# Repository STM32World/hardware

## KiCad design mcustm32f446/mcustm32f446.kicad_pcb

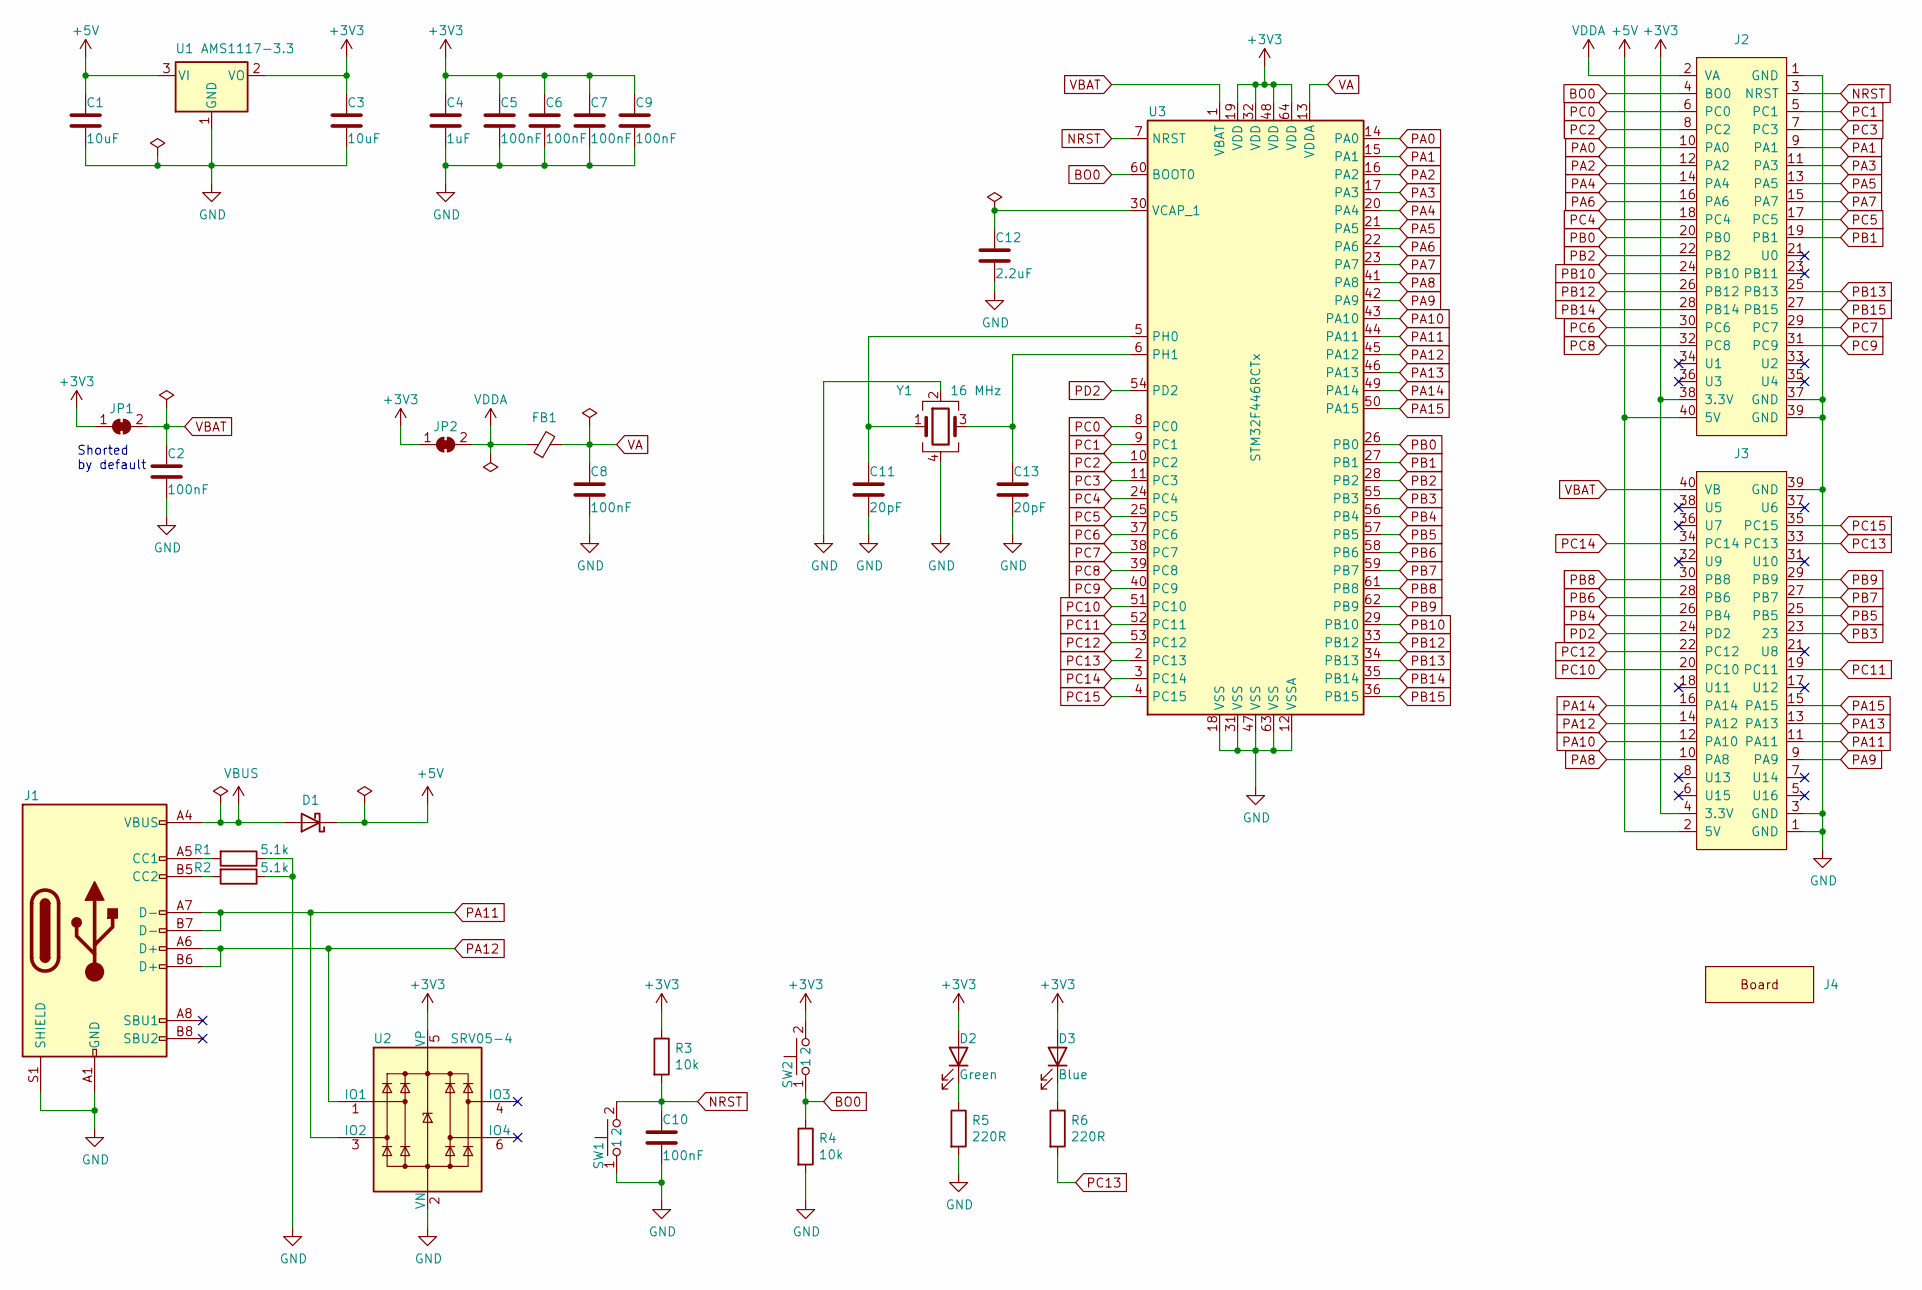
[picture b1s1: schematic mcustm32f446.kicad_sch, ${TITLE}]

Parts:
C1, C3: C_10UF_0805; C_0805_2012Metric; LCSC C15850
C2, C5, C6, C7, C8, C9, C10: C_100NF_0603; C_0603_1608Metric; LCSC C14663
C4: C_1UF_0603; C_0603_1608Metric; LCSC C15849
C11, C13: C_20PF_0603; C_0603_1608Metric; LCSC C1648
C12: C_2.2UF_0603; C_0603_1608Metric; LCSC C23630
D1: D_SOD-123; LCSC C8598
D2: LED_GREEN_0603; LED_0603_1608Metric; LCSC C72043
D3: LED_BLUE_0603; LED_0603_1608Metric; LCSC C72041
FB1: FB_0603; L_0603_1608Metric; LCSC C1002
J1: USB_C_Receptacle_HRO_TYPE-C-31-M-12; LCSC C165948
J2: STM32WORLD_CONNECTOR_1; PinSocket_2x20_P2.54mm_Vertical_Stackable; LCSC C35165
J3: STM32WORLD_CONNECTOR_2; PinSocket_2x20_P2.54mm_Vertical_Stackable; LCSC C35165
J4: STM32WORLD_BOARD
JP1, JP2: SolderJumper_2_Bridged; SolderJumper-2_P1.3mm_Bridged_RoundedPad1.0x1.5mm
R1, R2: R_5.1K_0603; R_0603_1608Metric; LCSC C23186
R3, R4: R_10K_0603; R_0603_1608Metric; LCSC C25804
R5, R6: R_220_0603; R_0603_1608Metric; LCSC C22962
SW1, SW2: TS-1088R-02526; LCSC C455281
U1: AMS1117-3.3; SOT-223-3_TabPin2; LCSC C6186
U2: SRV05-4; SOT-23-6; LCSC C85364
U3: STM32F446RCTx; LQFP-64_10x10mm_P0.5mm; LCSC C915971
Y1: X_16MHZ; Crystal_SMD_3225-4Pin_3.2x2.5mm; LCSC C13738

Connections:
+3V3: C3.1, C4.1, C5.1, C6.1, C7.1, C9.1, D2.2 (A), D3.2 (A), J2.38 (3.3V), J3.4 (3.3V), JP1.1 (A), JP2.1 (A), R3.1, SW2.2, U1.2 (VO), U2.5 (VP), U3.19 (VDD), U3.32 (VDD), U3.48 (VDD), U3.64 (VDD)
+5V: C1.1, D1.1 (K), J2.40 (5V), J3.2 (5V), U1.3 (VI)
BO0: J2.4 (BO0), R4.1, SW2.1, U3.60 (BOOT0)
GND: C1.2, C2.2, C3.2, C4.2, C5.2, C6.2, C7.2, C8.2, C9.2, C10.2, C11.2, C12.2, C13.2, J1.A1 (GND), J1.A12 (GND), J1.B1 (GND), J1.B12 (GND), J1.S1 (SHIELD), J2.1 (GND), J2.37 (GND), J2.39 (GND), J3.1 (GND), J3.3 (GND), J3.39 (GND), R1.1, R2.1, R4.2, R5.2, SW1.1, U1.1 (GND), U2.2 (VN), U3.12 (VSSA), U3.18 (VSS), U3.31 (VSS), U3.47 (VSS), U3.63 (VSS), Y1.2, Y1.4
NRST: C10.1, J2.3 (NRST), R3.2, SW1.2, U3.7 (NRST)
unnamed: C11.1, U3.5 (PH0), Y1.1
unnamed: C12.1, U3.30 (VCAP_1)
unnamed: C13.1, U3.6 (PH1), Y1.3
unnamed: D2.1 (K), R5.1
unnamed: D3.1 (K), R6.1
unnamed: J1.A5 (CC1), R1.2
unnamed: J1.B5 (CC2), R2.2
PA0: J2.10 (PA0), U3.14 (PA0)
PA1: J2.9 (PA1), U3.15 (PA1)
PA2: J2.12 (PA2), U3.16 (PA2)
PA3: J2.11 (PA3), U3.17 (PA3)
PA4: J2.14 (PA4), U3.20 (PA4)
PA5: J2.13 (PA5), U3.21 (PA5)
PA6: J2.16 (PA6), U3.22 (PA6)
PA7: J2.15 (PA7), U3.23 (PA7)
PA8: J3.10 (PA8), U3.41 (PA8)
PA9: J3.9 (PA9), U3.42 (PA9)
PA10: J3.12 (PA10), U3.43 (PA10)
PA11: J1.A7 (D-), J1.B7 (D-), J3.11 (PA11), U2.3 (IO2), U3.44 (PA11)
PA12: J1.A6 (D+), J1.B6 (D+), J3.14 (PA12), U2.1 (IO1), U3.45 (PA12)
PA13: J3.13 (PA13), U3.46 (PA13)
PA14: J3.16 (PA14), U3.49 (PA14)
PA15: J3.15 (PA15), U3.50 (PA15)
PB0: J2.20 (PB0), U3.26 (PB0)
PB1: J2.19 (PB1), U3.27 (PB1)
PB2: J2.22 (PB2), U3.28 (PB2)
PB3: J3.23, U3.55 (PB3)
PB4: J3.26 (PB4), U3.56 (PB4)
PB5: J3.25 (PB5), U3.57 (PB5)
PB6: J3.28 (PB6), U3.58 (PB6)
PB7: J3.27 (PB7), U3.59 (PB7)
PB8: J3.30 (PB8), U3.61 (PB8)
PB9: J3.29 (PB9), U3.62 (PB9)
PB10: J2.24 (PB10), U3.29 (PB10)
PB12: J2.26 (PB12), U3.33 (PB12)
PB13: J2.25 (PB13), U3.34 (PB13)
PB14: J2.28 (PB14), U3.35 (PB14)
PB15: J2.27 (PB15), U3.36 (PB15)
PC0: J2.6 (PC0), U3.8 (PC0)
PC1: J2.5 (PC1), U3.9 (PC1)
PC2: J2.8 (PC2), U3.10 (PC2)
PC3: J2.7 (PC3), U3.11 (PC3)
PC4: J2.18 (PC4), U3.24 (PC4)
PC5: J2.17 (PC5), U3.25 (PC5)
PC6: J2.30 (PC6), U3.37 (PC6)
PC7: J2.29 (PC7), U3.38 (PC7)
PC8: J2.32 (PC8), U3.39 (PC8)
PC9: J2.31 (PC9), U3.40 (PC9)
PC10: J3.20 (PC10), U3.51 (PC10)
PC11: J3.19 (PC11), U3.52 (PC11)
PC12: J3.22 (PC12), U3.53 (PC12)
PC13: J3.33 (PC13), R6.2, U3.2 (PC13)
PC14: J3.34 (PC14), U3.3 (PC14)
PC15: J3.35 (PC15), U3.4 (PC15)
PD2: J3.24 (PD2), U3.54 (PD2)
VA: C8.1, FB1.2, U3.13 (VDDA)
VBAT: C2.1, J3.40 (VB), JP1.2 (B), U3.1 (VBAT)
VBUS: D1.2 (A), J1.A4 (VBUS), J1.A9 (VBUS), J1.B4 (VBUS), J1.B9 (VBUS)
VDDA: FB1.1, J2.2 (VA), JP2.2 (B)

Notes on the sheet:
Shorted by default

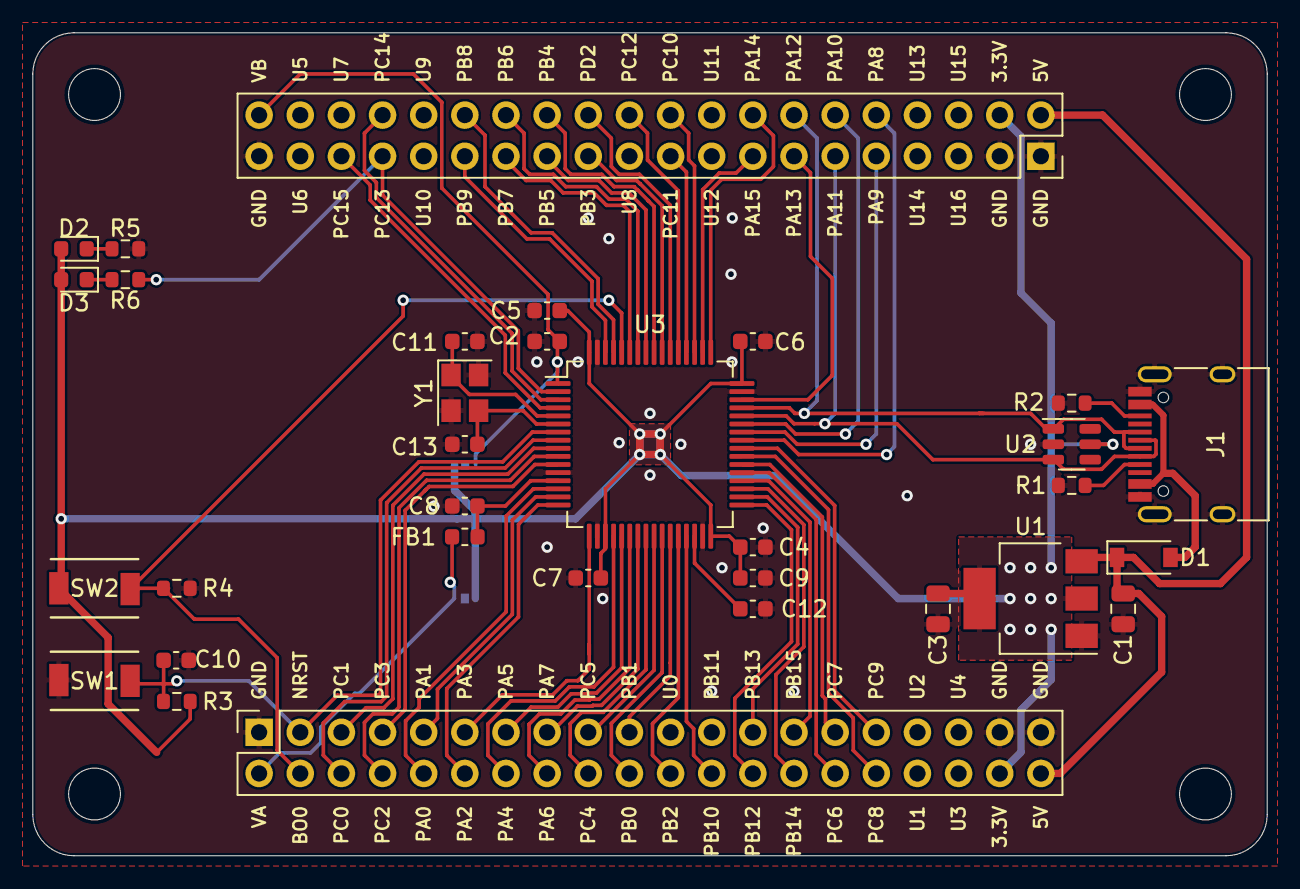
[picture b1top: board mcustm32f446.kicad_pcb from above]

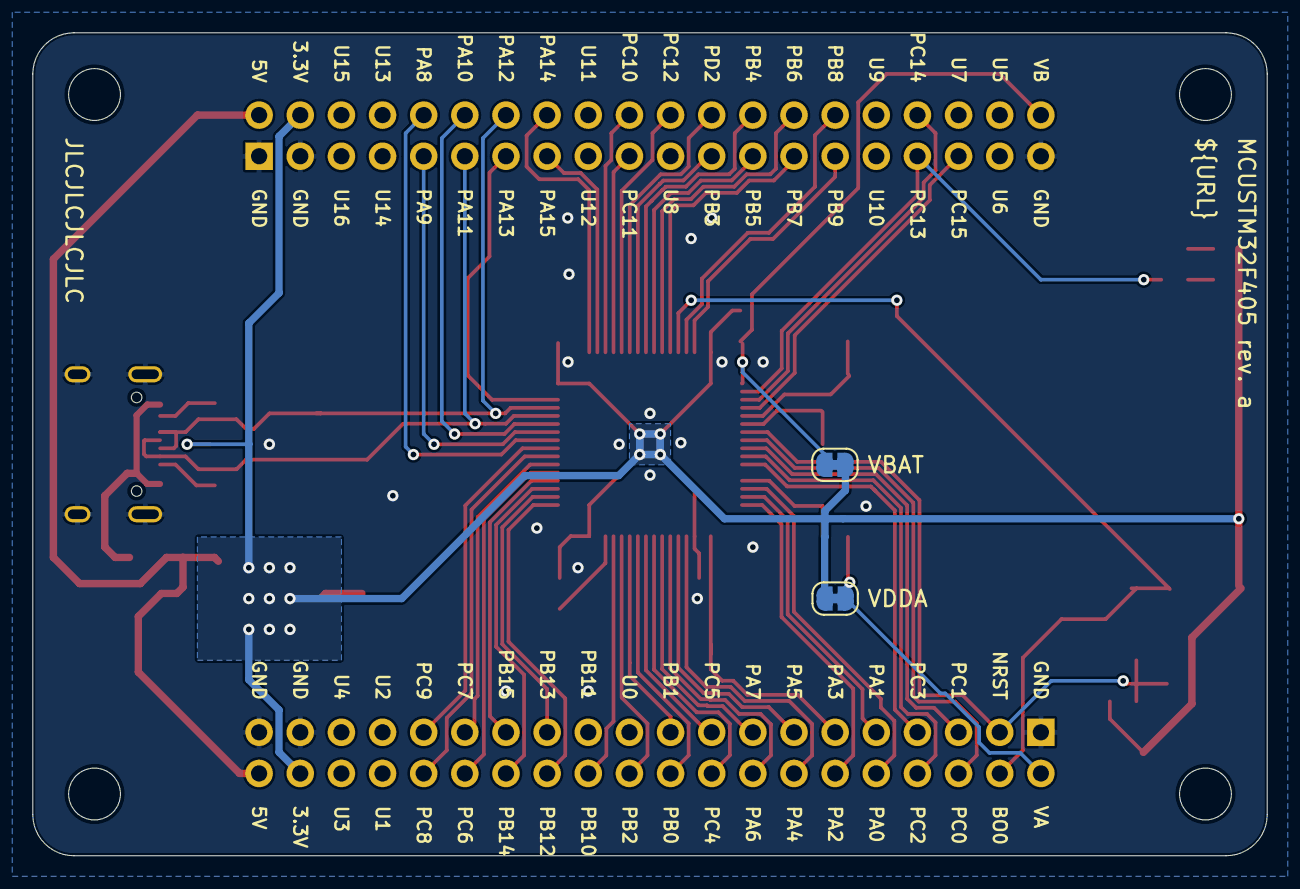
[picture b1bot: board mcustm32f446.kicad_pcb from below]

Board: 2 copper layers, 76.2 x 50.8 mm, 35 parts (2 on the bottom side), 64 nets.

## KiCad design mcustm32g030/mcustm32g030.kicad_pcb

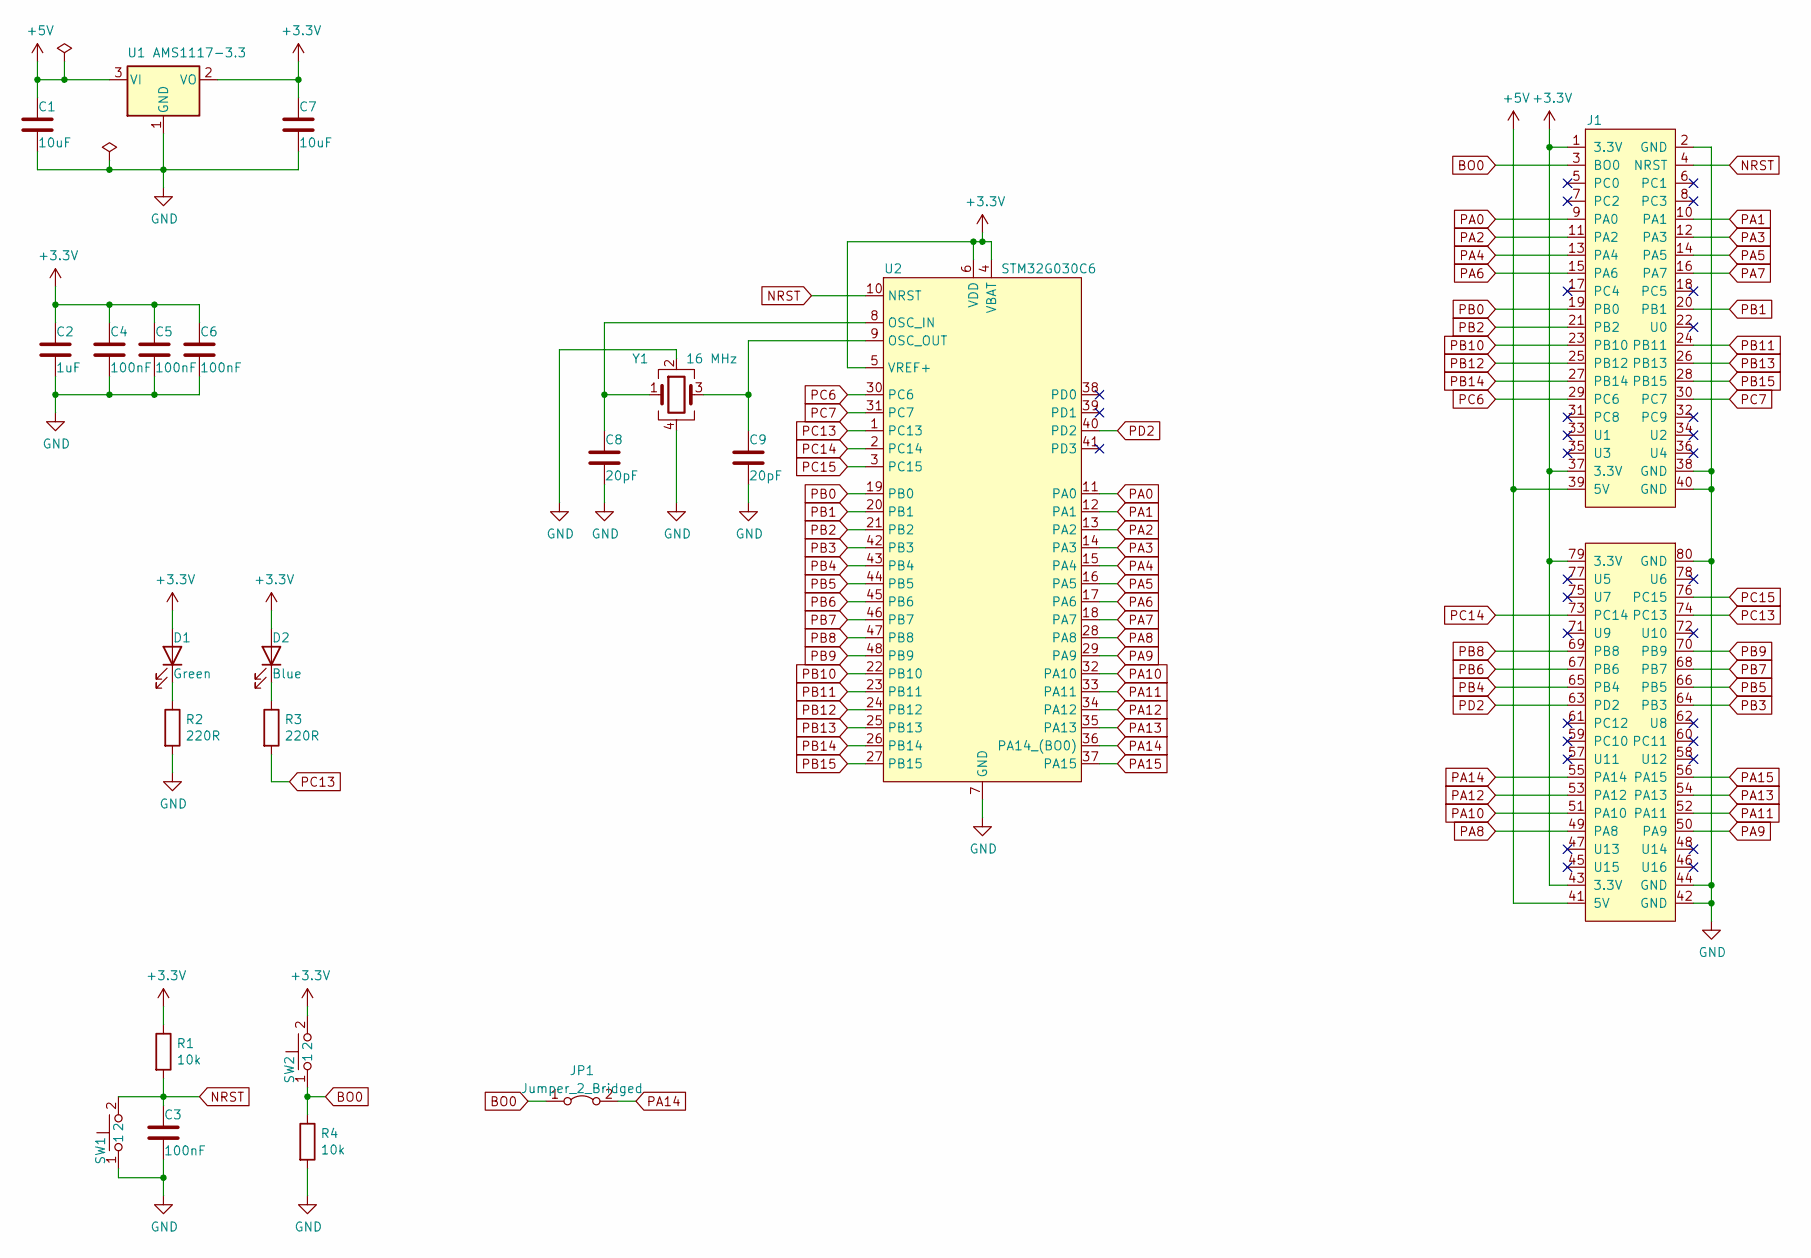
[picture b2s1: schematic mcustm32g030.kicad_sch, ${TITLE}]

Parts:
C1, C7: 10uF; C_0805_2012Metric; LCSC C15850
C2: 1uF; C_0603_1608Metric; LCSC C15849
C3, C4, C5, C6: 100nF; C_0603_1608Metric; LCSC C14663
C8, C9: 20pF; C_0603_1608Metric; LCSC C1648
D1: GR; LED_0603_1608Metric; LCSC C72043
D2: BL; LED_0603_1608Metric; LCSC C72041
J1: STM32WORLD_BASE
JP1: Jumper_2_Bridged; SolderJumper-2_P1.3mm_Bridged2Bar_Pad1.0x1.5mm
R1, R4: 10k; R_0603_1608Metric; LCSC C25804
R2, R3: 220R; R_0603_1608Metric; LCSC C22962
SW1, SW2: TS-1088R-02526; LCSC C455281
U1: AMS1117-3.3; SOT-223-3_TabPin2; LCSC C6186
U2: STM32G030C6; LQFP-48_7x7mm_P0.5mm; LCSC C529328
Y1: X_16MHZ; Crystal_SMD_3225-4Pin_3.2x2.5mm; LCSC C13738

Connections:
+3V3: C2.1, C4.1, C5.1, C6.1, C7.1, D1.2 (A), D2.2 (A), J1.1 (3.3V), J1.37 (3.3V), J1.43 (3.3V), J1.79 (3.3V), R1.1, SW2.2, U1.2 (VO), U2.4 (VBAT), U2.5 (VREF+), U2.6 (VDD)
+5V: C1.1, J1.39 (5V), J1.41 (5V), U1.3 (VI)
BO0: J1.3 (BO0), JP1.1 (A), R4.1, SW2.1
GND: C1.2, C2.2, C3.2, C4.2, C5.2, C6.2, C7.2, C8.2, C9.2, J1.2 (GND), J1.38 (GND), J1.40 (GND), J1.42 (GND), J1.44 (GND), J1.80 (GND), R2.2, R4.2, SW1.1, U1.1 (GND), U2.7 (GND), Y1.2, Y1.4
NRST: C3.1, J1.4 (NRST), R1.2, SW1.2, U2.10 (NRST)
unnamed: C8.1, U2.8 (OSC_IN), Y1.1
unnamed: C9.1, U2.9 (OSC_OUT), Y1.3
unnamed: D1.1 (K), R2.1
unnamed: D2.1 (K), R3.1
PA0: J1.9 (PA0), U2.11 (PA0)
PA1: J1.10 (PA1), U2.12 (PA1)
PA2: J1.11 (PA2), U2.13 (PA2)
PA3: J1.12 (PA3), U2.14 (PA3)
PA4: J1.13 (PA4), U2.15 (PA4)
PA5: J1.14 (PA5), U2.16 (PA5)
PA6: J1.15 (PA6), U2.17 (PA6)
PA7: J1.16 (PA7), U2.18 (PA7)
PA8: J1.49 (PA8), U2.28 (PA8)
PA9: J1.50 (PA9), U2.29 (PA9)
PA10: J1.51 (PA10), U2.32 (PA10)
PA11: J1.52 (PA11), U2.33 (PA11)
PA12: J1.53 (PA12), U2.34 (PA12)
PA13: J1.54 (PA13), U2.35 (PA13)
PA14: J1.55 (PA14), JP1.2 (B), U2.36 (PA14_(BO0))
PA15: J1.56 (PA15), U2.37 (PA15)
PB0: J1.19 (PB0), U2.19 (PB0)
PB1: J1.20 (PB1), U2.20 (PB1)
PB2: J1.21 (PB2), U2.21 (PB2)
PB3: J1.64 (PB3), U2.42 (PB3)
PB4: J1.65 (PB4), U2.43 (PB4)
PB5: J1.66 (PB5), U2.44 (PB5)
PB6: J1.67 (PB6), U2.45 (PB6)
PB7: J1.68 (PB7), U2.46 (PB7)
PB8: J1.69 (PB8), U2.47 (PB8)
PB9: J1.70 (PB9), U2.48 (PB9)
PB10: J1.23 (PB10), U2.22 (PB10)
PB11: J1.24 (PB11), U2.23 (PB11)
PB12: J1.25 (PB12), U2.24 (PB12)
PB13: J1.26 (PB13), U2.25 (PB13)
PB14: J1.27 (PB14), U2.26 (PB14)
PB15: J1.28 (PB15), U2.27 (PB15)
PC6: J1.29 (PC6), U2.30 (PC6)
PC7: J1.30 (PC7), U2.31 (PC7)
PC13: J1.74 (PC13), R3.2, U2.1 (PC13)
PC14: J1.73 (PC14), U2.2 (PC14)
PC15: J1.76 (PC15), U2.3 (PC15)
PD2: J1.63 (PD2), U2.40 (PD2)

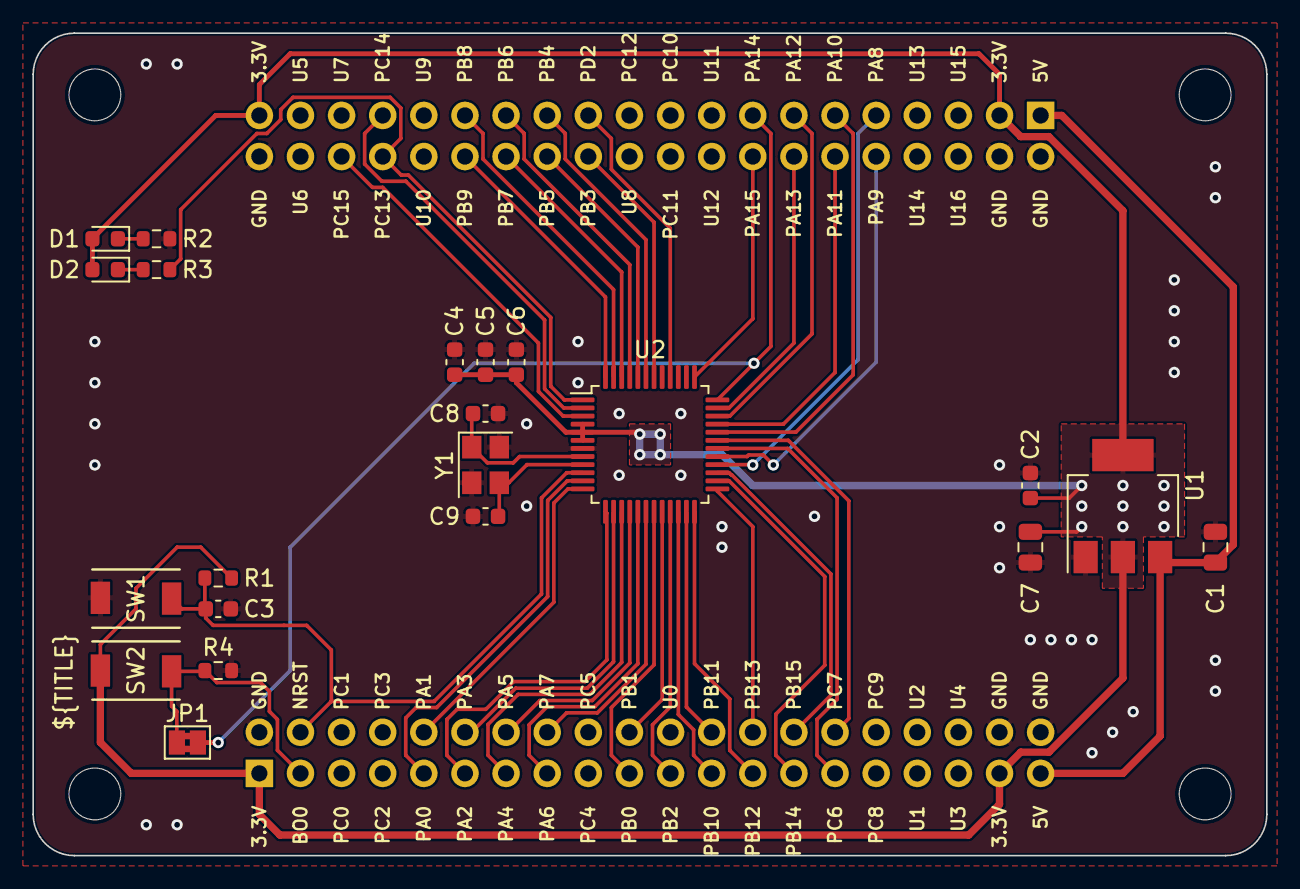
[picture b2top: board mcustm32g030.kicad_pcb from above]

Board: 2 copper layers, 76.2 x 50.8 mm, 22 parts (0 on the bottom side), 47 nets.

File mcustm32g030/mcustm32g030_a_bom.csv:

Comment,Designator,Footprint,Display,LCSC
"10uF","C1,C7","Capacitor_SMD:C_0805_2012Metric","10uF","C15850"
"1uF","C2","Capacitor_SMD:C_0603_1608Metric","1uF","C15849"
"100nF","C3,C4,C5,C6","Capacitor_SMD:C_0603_1608Metric","100nF","C14663"
"20pF","C8,C9","Capacitor_SMD:C_0603_1608Metric","20pF","C1648"
"GR","D1","LED_SMD:LED_0603_1608Metric","Green","C72043"
"BL","D2","LED_SMD:LED_0603_1608Metric","Blue","C72041"
"STM32WORLD_BASE","J1","stm32world:STM32WORLD_BASE"
"Jumper_2_Bridged","JP1","Jumper:SolderJumper-2_P1.3mm_Bridged2Bar_Pad1.0x1.5mm"
"10k","R1,R4","Resistor_SMD:R_0603_1608Metric","10k","C25804"
"220R","R2,R3","Resistor_SMD:R_0603_1608Metric","220R","C22962"
"~","SW1,SW2","stm32world:TS-1088R-02526","","C455281"
"AMS1117-3.3","U1","Package_TO_SOT_SMD:SOT-223-3_TabPin2","","C6186"
"STM32G030C6","U2","Package_QFP:LQFP-48_7x7mm_P0.5mm","","C529328"
"X_16MHZ","Y1","Crystal:Crystal_SMD_3225-4Pin_3.2x2.5mm","16 MHz","C13738"

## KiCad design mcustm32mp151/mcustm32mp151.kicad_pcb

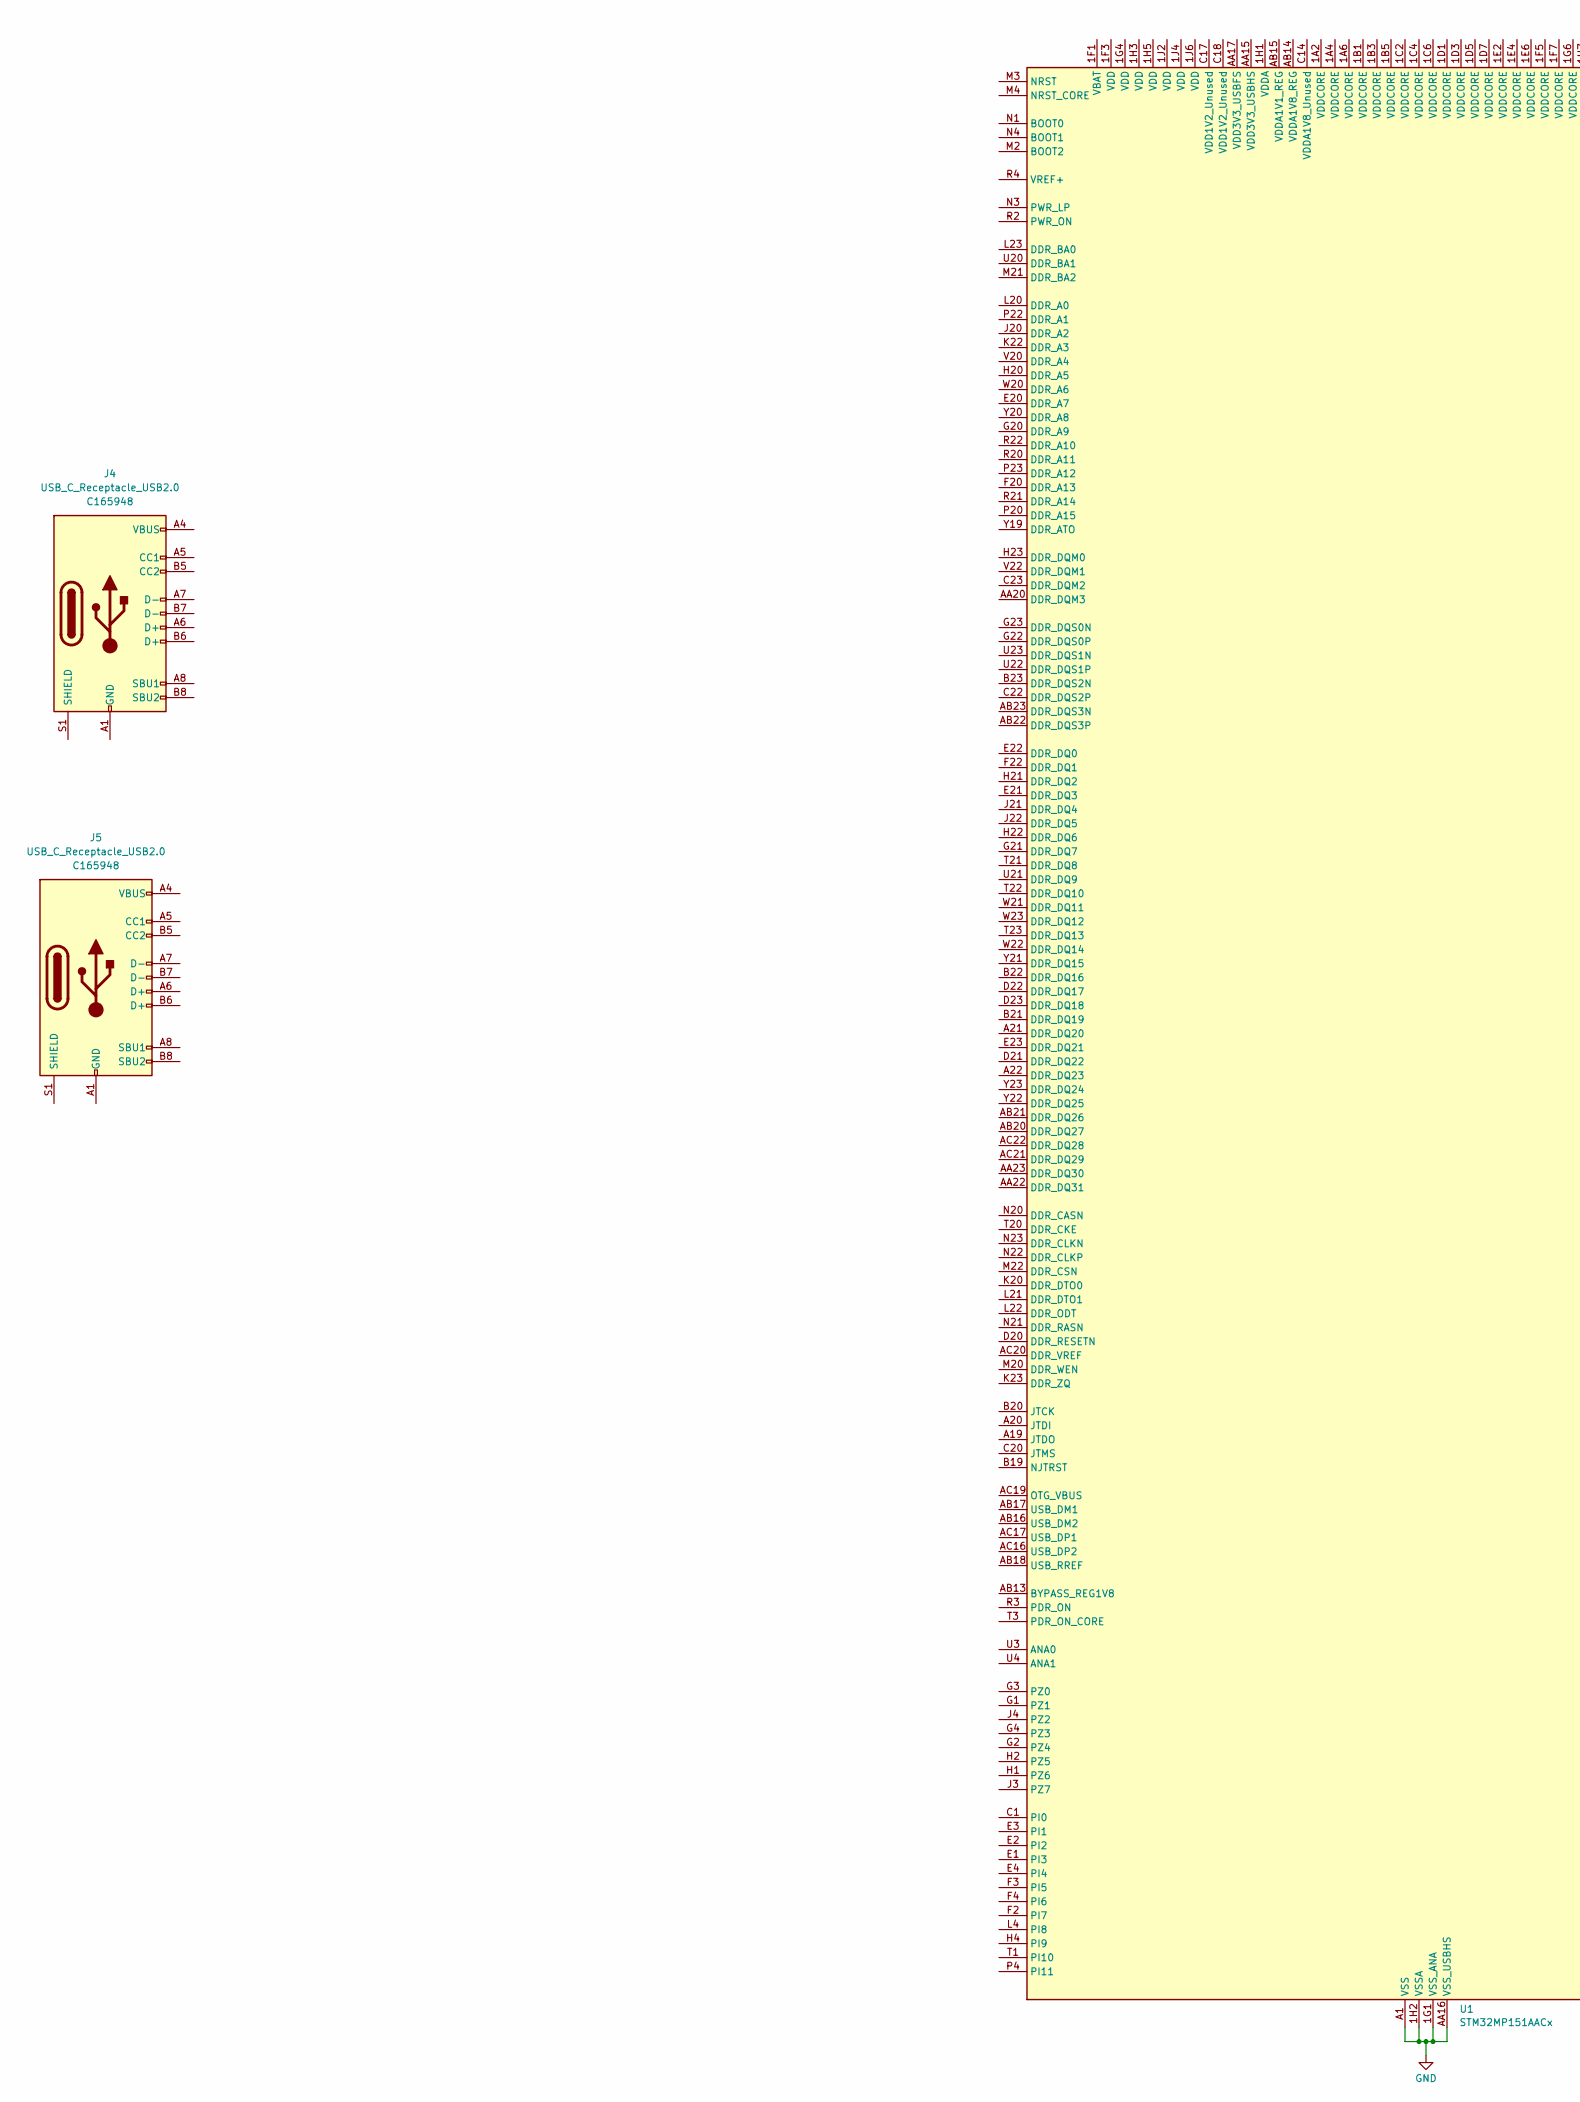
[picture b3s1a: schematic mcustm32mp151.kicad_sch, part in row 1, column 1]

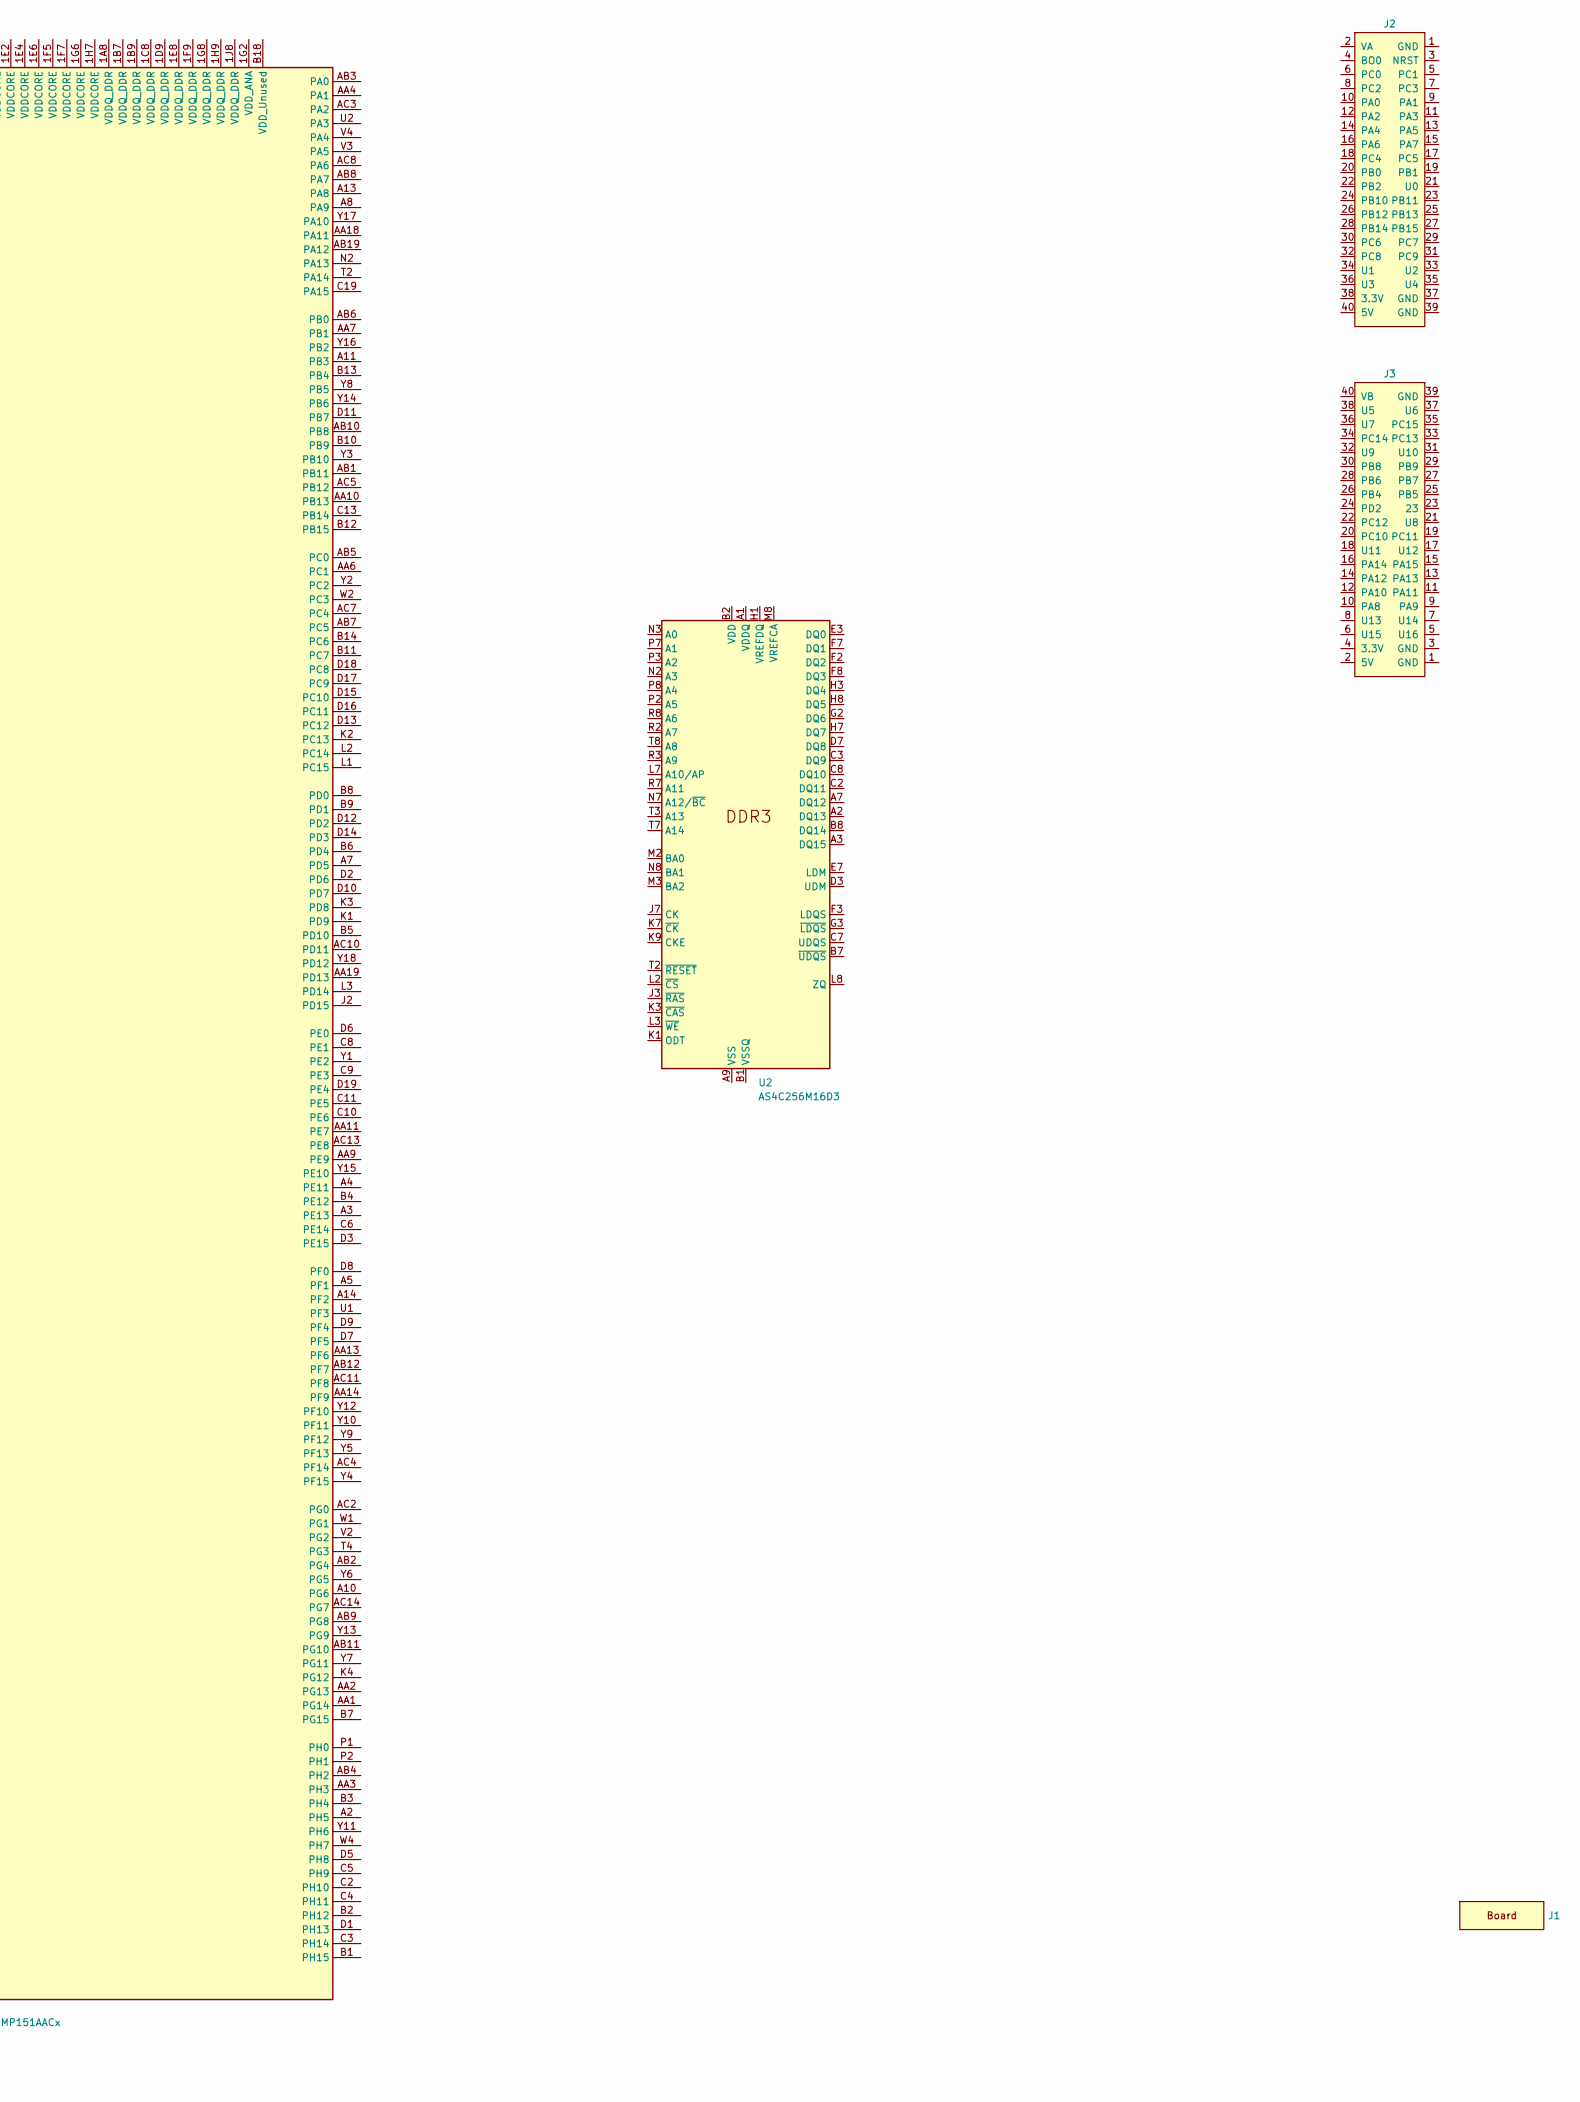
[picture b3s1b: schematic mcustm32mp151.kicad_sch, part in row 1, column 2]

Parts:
J1: STM32WORLD_BOARD
J2: STM32WORLD_CONNECTOR_1; PinSocket_2x20_P2.54mm_Vertical_Stackable; LCSC C35165
J3: STM32WORLD_CONNECTOR_2; PinSocket_2x20_P2.54mm_Vertical_Stackable; LCSC C35165
J4, J5: USB_C_Receptacle_USB2.0; USB_C_Receptacle_HRO_TYPE-C-31-M-12; LCSC C165948
U1: STM32MP151AACx; ST_TFBGA-361_12x12mm_Layout23x23_P0.5mmP0.65mm; LCSC C1555473
U2: AS4C256M16D3; BGA-96_9.0x13.0mm_Layout2x3x16_P0.8mm

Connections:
GND: U1.1A3 (VSS), U1.1A5 (VSS), U1.1A7 (VSS), U1.1B2 (VSS), U1.1B4 (VSS), U1.1B6 (VSS), U1.1B8 (VSS), U1.1C1 (VSS), U1.1C3 (VSS), U1.1C5 (VSS), U1.1C7 (VSS), U1.1C9 (VSS), U1.1D2 (VSS), U1.1D4 (VSS), U1.1D6 (VSS), U1.1D8 (VSS), U1.1E1 (VSS), U1.1E3 (VSS), U1.1E5 (VSS), U1.1E7 (VSS), U1.1E9 (VSS), U1.1F2 (VSS), U1.1F4 (VSS), U1.1F6 (VSS), U1.1F8 (VSS), U1.1G1 (VSS_ANA), U1.1G3 (VSS), U1.1G5 (VSS), U1.1G7 (VSS), U1.1G9 (VSS), U1.1H2 (VSSA), U1.1H4 (VSS), U1.1H6 (VSS), U1.1H8 (VSS), U1.1J3 (VSS), U1.1J5 (VSS), U1.1J7 (VSS), U1.A1 (VSS), U1.A23 (VSS), U1.AA5 (VSS), U1.AA8 (VSS), U1.AA12 (VSS), U1.AA16 (VSS_USBHS), U1.AA21 (VSS), U1.AC1 (VSS), U1.AC23 (VSS), U1.C7 (VSS), U1.C12 (VSS), U1.C16 (VSS), U1.C21 (VSS), U1.D4 (VSS), U1.F21 (VSS), U1.H3 (VSS), U1.K21 (VSS), U1.P3 (VSS), U1.P21 (VSS), U1.V21 (VSS), U1.W3 (VSS)
unnamed: J4.A1 (GND), J4.A12 (GND), J4.B1 (GND), J4.B12 (GND)
unnamed: J4.A4 (VBUS), J4.A9 (VBUS), J4.B4 (VBUS), J4.B9 (VBUS)
unnamed: J5.A1 (GND), J5.A12 (GND), J5.B1 (GND), J5.B12 (GND)
unnamed: J5.A4 (VBUS), J5.A9 (VBUS), J5.B4 (VBUS), J5.B9 (VBUS)
unnamed: U2.B2 (VDD), U2.D9 (VDD), U2.G7 (VDD), U2.K2 (VDD), U2.K8 (VDD), U2.N1 (VDD), U2.N9 (VDD), U2.R1 (VDD), U2.R9 (VDD)
unnamed: U2.A1 (VDDQ), U2.A8 (VDDQ), U2.C1 (VDDQ), U2.C9 (VDDQ), U2.D2 (VDDQ), U2.E9 (VDDQ), U2.F1 (VDDQ), U2.H2 (VDDQ), U2.H9 (VDDQ)
unnamed: U2.A9 (VSS), U2.B3 (VSS), U2.E1 (VSS), U2.G8 (VSS), U2.J2 (VSS), U2.J8 (VSS), U2.M1 (VSS), U2.M9 (VSS), U2.P1 (VSS), U2.P9 (VSS), U2.T1 (VSS), U2.T9 (VSS)
unnamed: U2.B1 (VSSQ), U2.B9 (VSSQ), U2.D1 (VSSQ), U2.D8 (VSSQ), U2.E2 (VSSQ), U2.E8 (VSSQ), U2.F9 (VSSQ), U2.G1 (VSSQ), U2.G9 (VSSQ)

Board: 8 copper layers, 7 parts (0 on the bottom side), 9 nets, no tracks yet.

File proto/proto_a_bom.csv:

Comment,Designator,Footprint,LCSC
"STM32WORLD_CONNECTOR_2","J1","stm32world:PinSocket_2x20_P2.54mm_Vertical_Stackable","C35165"
"STM32WORLD_CONNECTOR_1","J2","stm32world:PinSocket_2x20_P2.54mm_Vertical_Stackable","C35165"
"STM32WORLD_BOARD","J3","stm32world:STM32WORLD_BOARD"
"TestPoint_Small","TP1,TP2,TP3,TP4,TP5,TP6,TP7,TP8,TP9,TP10,TP11,TP12,TP13,TP14,TP15,TP16,TP17,TP18,TP19,TP20,TP21,TP22,TP23,TP24,TP25,TP26,TP27,TP28,TP29,TP30,TP31,TP32,TP33,TP34,TP35,TP36,TP37,TP38,TP39,TP40,TP41,TP42,TP43,TP44,TP45,TP46,TP47,TP48,TP49,TP50,TP51,TP52,TP53,TP54,TP55,TP56,TP57,TP58,TP59,TP60,TP61,TP62,TP63,TP64,TP65,TP66,TP67,TP68,TP69,TP70,TP71,TP72,TP73,TP74,TP75,TP76,TP77,TP78,TP79,TP80,TP81,TP82,TP83,TP84,TP85,TP86,TP87,TP88,TP89,TP90,TP91,TP92,TP93,TP94,TP95,TP96,TP97,TP98,TP99,TP100,TP101,TP102,TP103,TP104,TP105,TP106,TP107,TP108,TP109,TP110,TP111,TP112,TP113,TP114,TP115,TP116,TP117,TP118,TP119,TP120,TP121,TP122,TP123,TP124,TP125,TP126,TP127,TP128,TP129,TP130,TP131,TP132,TP133,TP134,TP135,TP136,TP137,TP138,TP139,TP140,TP141,TP142,TP143,TP144,TP145,TP146,TP147,TP148,TP149,TP150,TP151,TP152,TP153,TP154,TP155,TP156,TP157,TP158,TP159,TP160,TP161,TP162,TP163,TP164,TP165,TP166,TP167,TP168,TP169,TP170,TP171,TP172,TP173,TP174,TP175,TP176,TP177,TP178,TP179,TP180,TP181,TP182,TP183,TP184,TP185,TP186,TP187,TP188,TP189,TP190,TP191,TP192,TP193,TP194,TP195,TP196,TP197,TP198,TP199,TP200,TP201,TP202,TP203,TP204,TP205,TP206,TP207,TP208,TP209,TP210,TP211,TP212,TP213,TP214,TP215,TP216,TP217,TP218,TP219,TP220,TP221,TP222,TP223,TP224,TP225,TP226,TP227,TP228,TP229,TP230,TP231,TP232,TP233,TP234,TP235,TP236,TP237,TP238,TP239,TP240,TP241,TP242,TP243,TP244,TP245,TP246,TP247,TP248,TP249,TP250,TP251,TP252,TP253,TP254,TP255,TP256,TP257,TP258,TP259,TP260,TP261,TP262,TP263,TP264,TP265,TP266,TP267,TP268,TP269,TP270,TP271,TP272,TP273,TP274,TP275,TP276,TP277,TP278,TP279,TP280,TP281,TP282,TP283,TP284,TP285,TP286,TP287,TP288,TP289,TP290,TP291,TP292,TP293,TP294,TP295,TP296,TP297,TP298,TP299,TP300,TP301,TP302,TP303,TP304","stm32world:PROTO_PAD"
